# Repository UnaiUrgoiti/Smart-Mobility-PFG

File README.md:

Hello Everyone,
This repository comes along with the development of a embedded platform for the provisioning of intelligent systems, a Deustotech research in the Smart-Mobility group.
The project was fully carried out by me, Unai Urgoiti Lopez de Luzuriaga, as my final project grade.

All the Files provided are original. They are distributed according their nature.
This repository includes the code used in the Jetson Nano, The Raspberry Pi 4 and the RPI Pico, along with the fabrication designs of the PCB and the 3D models and assemblies for the components.

I hope anyone reading this likes the project and if any question arises feel free to ask or send me an email at unai.urgoiti@opendeusto.es

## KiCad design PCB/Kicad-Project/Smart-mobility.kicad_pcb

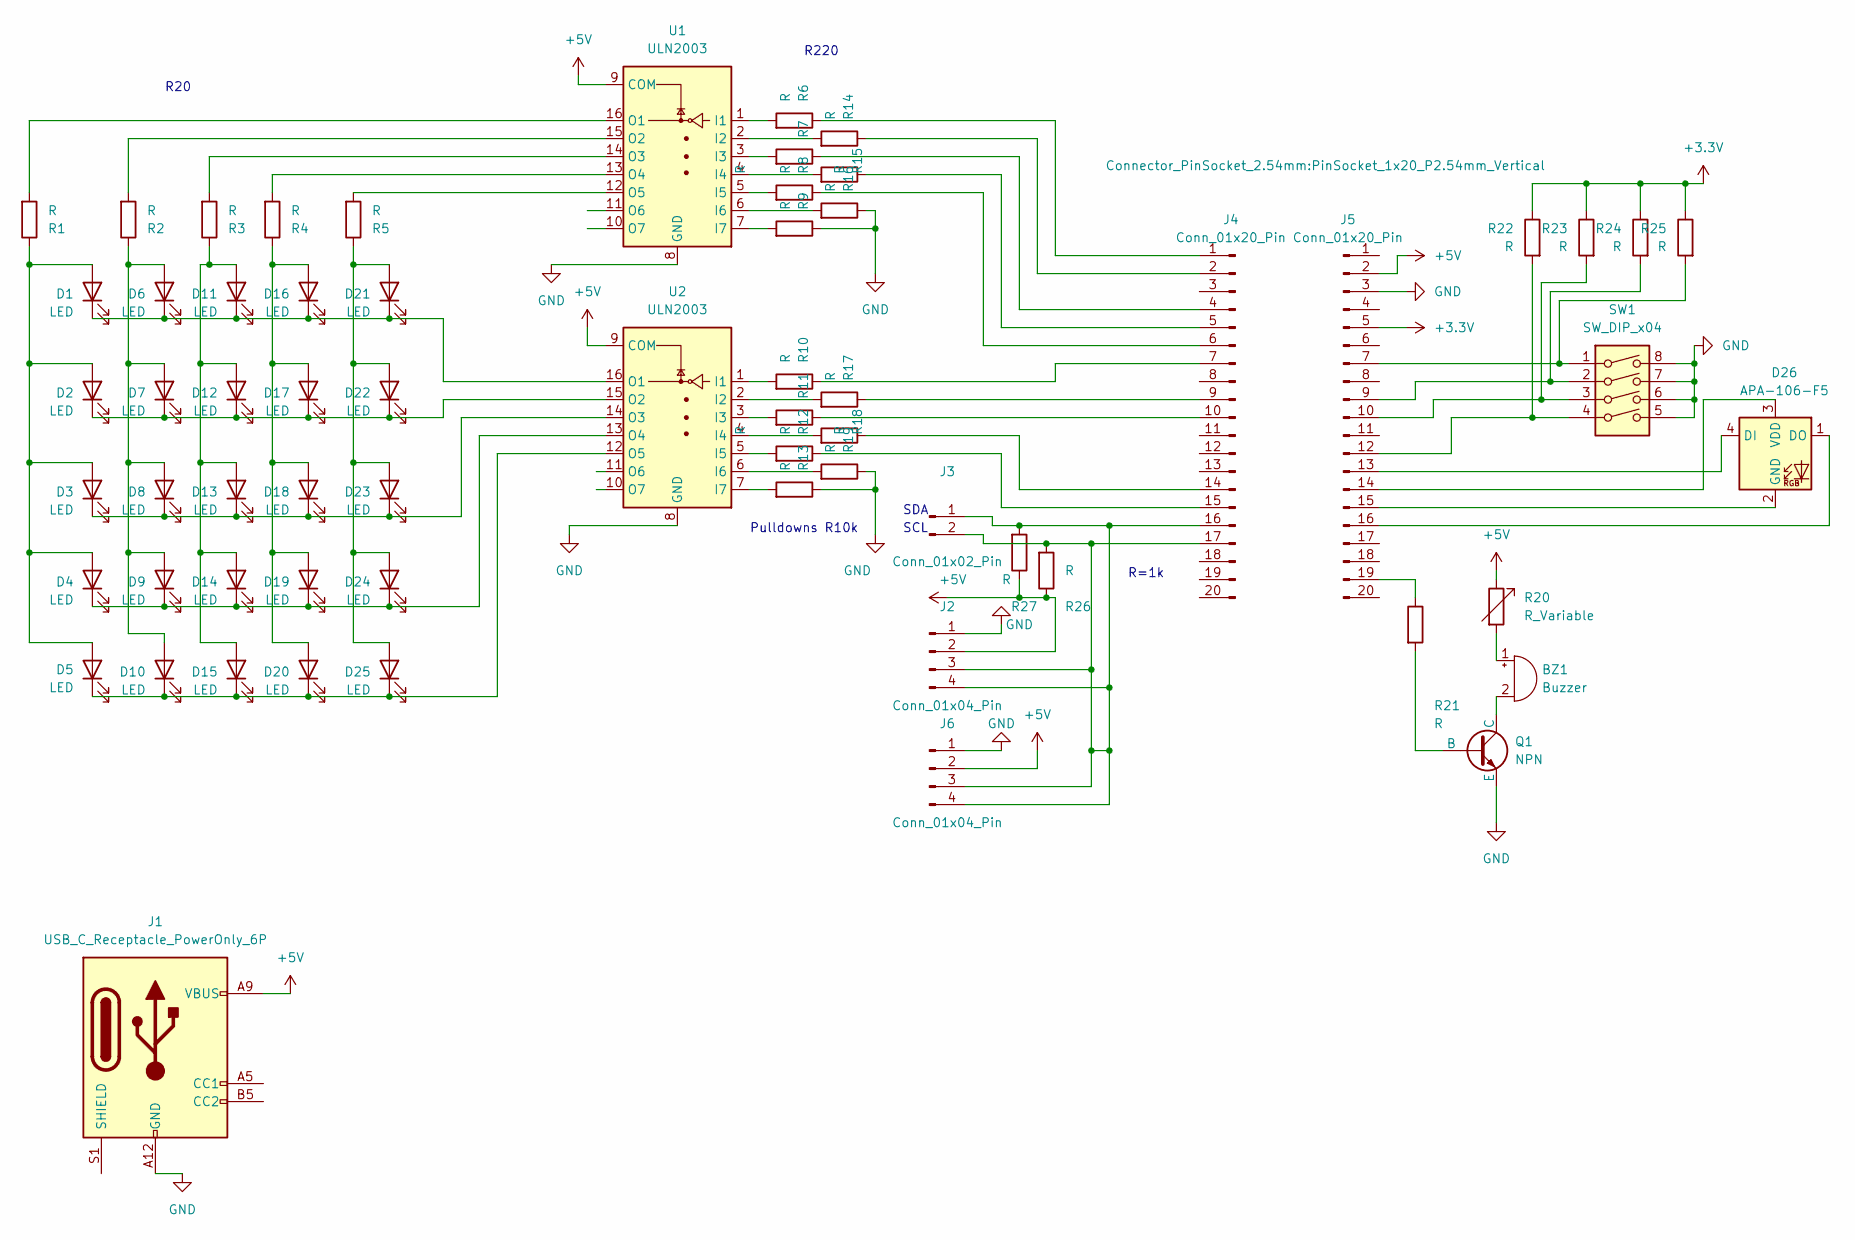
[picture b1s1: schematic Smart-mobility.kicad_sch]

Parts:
BZ1: Buzzer; MagneticBuzzer_ProSignal_ABI-009-RC
D1, D2, D3, D4, D5, D6, D7, D8, D9, D10, D11, D12, D13, D14, D15, D16, D17, D18, D19, D20, D21, D22, D23, D24, D25: LED; LED_PLCC-2_3.4x3.0mm_KA
D26: APA-106-F5; LED_D5.0mm-4_RGB
J1: USB_C_Receptacle_PowerOnly_6P; USB_C_Receptacle_GCT_USB4135-GF-A_6P_TopMnt_Horizontal
J2, J6: Conn_01x04_Pin; PinSocket_1x04_P2.54mm_Vertical
J3: Conn_01x02_Pin; PinSocket_1x02_P2.54mm_Horizontal
J4, J5: Conn_01x20_Pin; PinSocket_1x20_P2.54mm_Vertical
Q1: NPN; TO-18_4
R1, R2, R3, R4, R5, R6, R7, R8, R9, R10, R11, R12, R13, R14, R15, R16, R17, R18, R19, R22, R23, R24, R25, R26, R27: R; R_1210_3225Metric
R20: R_Variable; Potentiometer_Piher_PT-6-V_Vertical
R21: R; R_Axial_DIN0207_L6.3mm_D2.5mm_P10.16mm_Horizontal
SW1: SW_DIP_x04; PinHeader_2x04_P2.54mm_Vertical
U1, U2: ULN2003; D0016A_L

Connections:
+3.3V: J5.5, R22.1, R23.1, R24.1, R25.1
+5V: J1.A9 (VBUS), J1.B9 (VBUS), J2.2, J5.2, J6.2, R20.1, R26.1, R27.1, U1.9 (COM), U2.9 (COM)
GND: J1.A12 (GND), J1.B12 (GND), J2.1, J5.3, J6.1, Q1.3 (E), R9.1, R13.1, R16.1, R19.1, SW1.5, SW1.6, SW1.7, SW1.8, U1.8 (GND), U2.8 (GND)
unnamed: BZ1.2 (+), Q1.1 (C)
unnamed: BZ1.1 (-), R20.2
unnamed: D1.2 (A), D2.2 (A), D3.2 (A), D4.2 (A), D5.2 (A), R1.1
unnamed: D1.1 (K), D6.1 (K), D11.1 (K), D16.1 (K), D21.1 (K), U2.16 (O1)
unnamed: D6.2 (A), D7.2 (A), D8.2 (A), D9.2 (A), D10.2 (A), R2.1
unnamed: D5.1 (K), D10.1 (K), D15.1 (K), D20.1 (K), D25.1 (K), U2.12 (O5)
unnamed: D11.2 (A), D12.2 (A), D13.2 (A), D14.2 (A), D15.2 (A), R3.1
unnamed: D2.1 (K), D7.1 (K), D12.1 (K), D17.1 (K), D22.1 (K), U2.15 (O2)
unnamed: D3.1 (K), D8.1 (K), D13.1 (K), D18.1 (K), D23.1 (K), U2.14 (O3)
unnamed: D4.1 (K), D9.1 (K), D14.1 (K), D19.1 (K), D24.1 (K), U2.13 (O4)
unnamed: D16.2 (A), D17.2 (A), D18.2 (A), D19.2 (A), D20.2 (A), R4.1
unnamed: D21.2 (A), D22.2 (A), D23.2 (A), D24.2 (A), D25.2 (A), R5.1
unnamed: D26.4 (DI), J5.13
unnamed: D26.1 (DO), J5.16
unnamed: D26.2 (GND), J5.15
unnamed: D26.3 (VDD), J5.14
unnamed: J4.1, R6.1
unnamed: J4.2, R14.1
unnamed: J4.4, R7.1
unnamed: J4.5, R15.1
unnamed: J4.6, R8.1
unnamed: J4.7, R10.1
unnamed: J4.9, R17.1
unnamed: J4.10, R11.1
unnamed: J4.14, R18.1
unnamed: J4.15, R12.1
unnamed: J5.7, R25.2, SW1.1
unnamed: J5.9, R24.2, SW1.2
unnamed: J5.10, R23.2, SW1.3
unnamed: J5.12, R22.2, SW1.4
unnamed: J5.19, R21.1
unnamed: Q1.2 (B), R21.2
unnamed: R6.2, U1.1 (I1)
unnamed: R14.2, U1.2 (I2)
unnamed: R7.2, U1.3 (I3)
unnamed: R15.2, U1.4 (I4)
unnamed: R8.2, U1.5 (I5)
unnamed: R16.2, U1.6 (I6)
unnamed: R9.2, U1.7 (I7)
unnamed: R1.2, U1.16 (O1)
unnamed: R2.2, U1.15 (O2)
unnamed: R3.2, U1.14 (O3)
unnamed: R4.2, U1.13 (O4)
unnamed: R5.2, U1.12 (O5)
unnamed: R10.2, U2.1 (I1)
unnamed: R17.2, U2.2 (I2)
unnamed: R11.2, U2.3 (I3)
unnamed: R18.2, U2.4 (I4)
unnamed: R12.2, U2.5 (I5)
unnamed: R19.2, U2.6 (I6)
unnamed: R13.2, U2.7 (I7)

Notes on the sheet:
SDA
SCL
R20
R=1k
R220
Pulldowns R10k

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
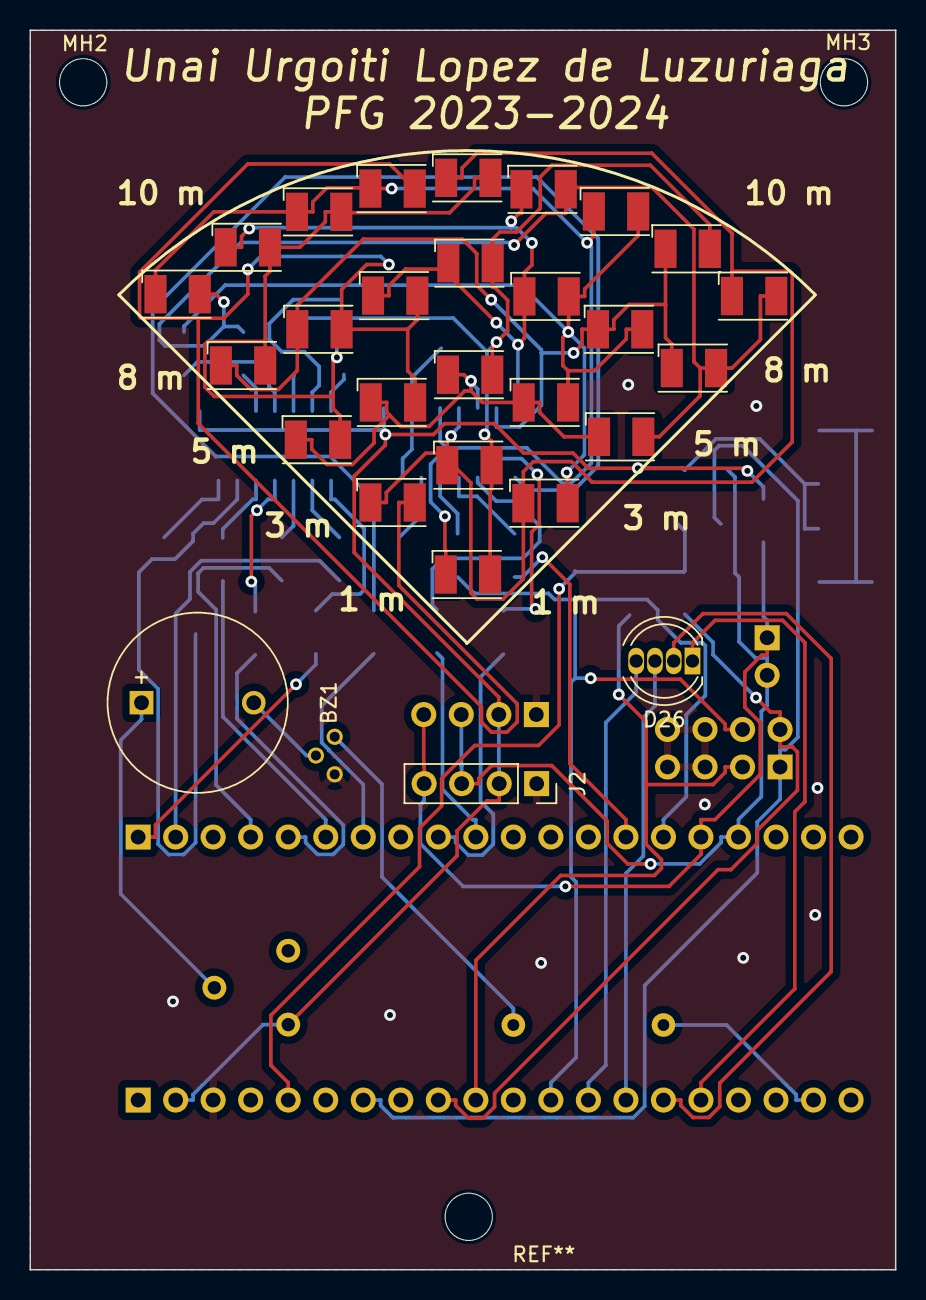
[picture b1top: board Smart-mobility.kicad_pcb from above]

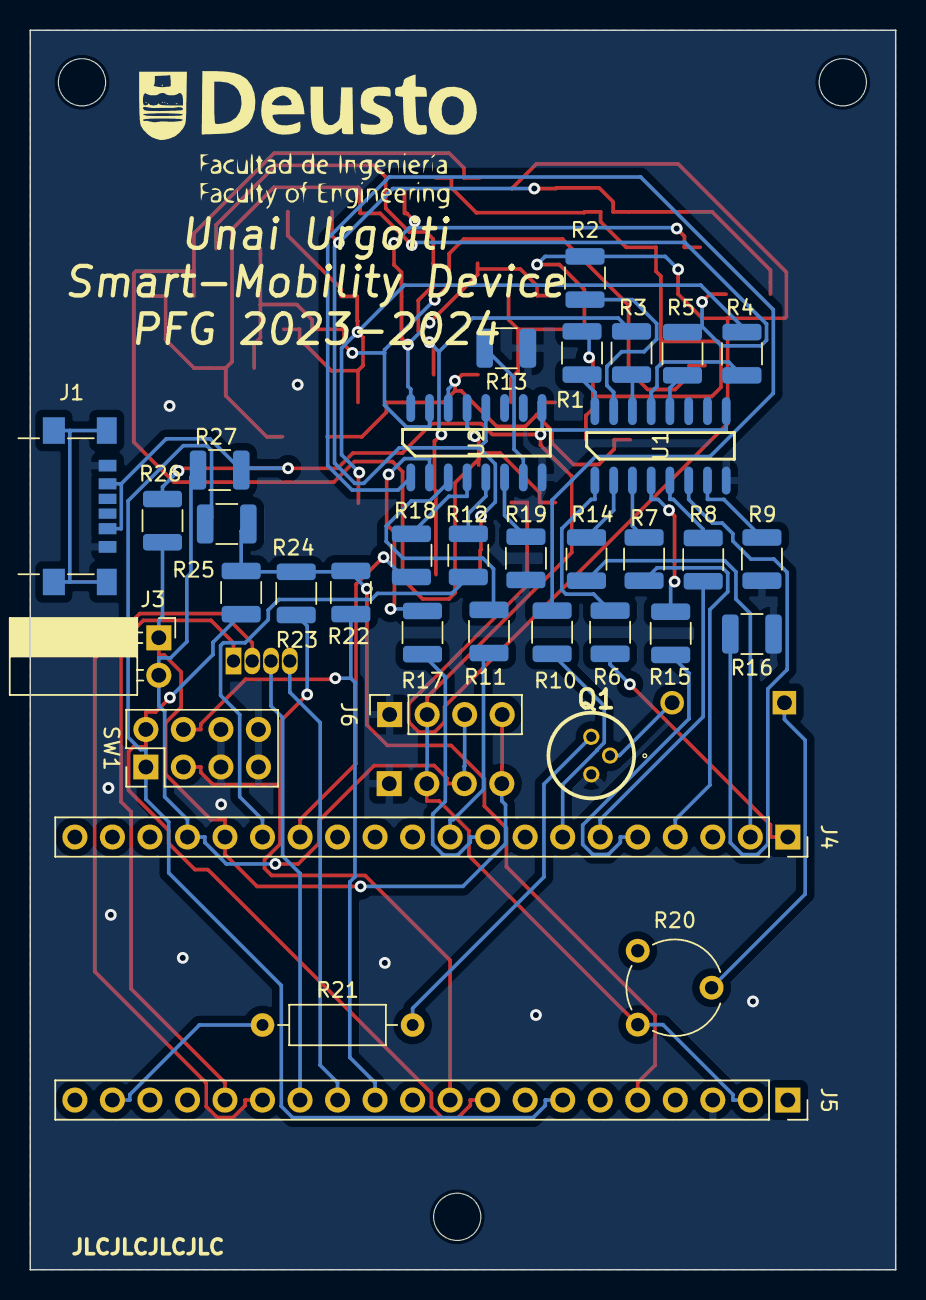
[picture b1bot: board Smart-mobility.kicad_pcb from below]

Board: 2 copper layers, 58.6 x 83.9 mm, 67 parts (37 on the bottom side), 56 nets.

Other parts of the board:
1: LOGO
MH2, MH3: MountingHole_3.2mm_M3

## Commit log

2024-06-08 Added Handlebar components
2024-06-08 Added Gerber files
2024-06-08 Added Frame Assembly Parts
2024-06-08 Updated Pieces
2024-06-12 Added JN/RPI4/RPIPIco
2024-06-12 Added Memory Document
2024-06-16 Updated documentation
